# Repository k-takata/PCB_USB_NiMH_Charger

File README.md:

# USB NiMH ゆっくり充電器 (USB NiMH Slow Charger) rev. 3

## 概要

[秋月電子](https://akizukidenshi.com/)の[いたわりNiCd充電器 キット](https://akizukidenshi.com/img/contents/kairo/%E3%83%87%E3%83%BC%E3%82%BF/%E5%85%85%E9%9B%BB%E5%99%A8%E9%96%A2%E4%BF%82/H001%E3%81%84%E3%81%9F%E3%82%8F%E3%82%8ANiCd_.pdf)を元に、USBを電源とし、ニッケル水素電池を1本単位で単3、単4それぞれ2本（合計4本）まで充電できるようにした充電器です。

## 使用したソフトウェア

KiCad 7.0

## 回路図

## 基板パターン図

## 部品表

| Reference            |個数|値    | 説明 |
|----------------------|----|------|------|
|BT1, BT2              |   2|      |[単4電池ボックス](https://akizukidenshi.com/catalog/g/g102670/)|
|BT3, BT4              |   2|      |[単3電池ボックス](https://akizukidenshi.com/catalog/g/g100308/)|
|C1, C4, C5, C6, C7, C8|   6|0.1μF|積層セラミックコンデンサー|
|C2                    |   1|100μF|電解コンデンサー φ5[^1]|
|C3                    |   1| 10μF|[積層セラミックコンデンサー 10μF](https://akizukidenshi.com/catalog/g/g103095/)|
|D1                    |   1|[11EQS03L](https://akizukidenshi.com/catalog/g/g108997/)|ショットキーバリアダイオード|
|D2, D3, D4, D5        |   4|      |[低消費赤色LED](https://akizukidenshi.com/catalog/g/g116914/)。眩しい場合は[LED光拡散キャップ](https://akizukidenshi.com/catalog/g/g101120/)が使える。|
|F1                    |   1|  1.1A|[ポリヒューズ](https://akizukidenshi.com/catalog/g/g100507/)|
|J1                    |   1|UJC-HP-3-SMT-TR|[USB Type-C コネクター 電源供給用](https://akizukidenshi.com/catalog/g/g116438/)|
|J2                    |   1|      |ピンヘッダー 1x2、強制充電用|
|Q1                    |   1|2SA1015||
|Q2, Q3, Q4, Q5        |   4|[2SB834](https://akizukidenshi.com/catalog/g/g108747/)|裏面に取り付け。他の代替候補としては[2SA1441](https://akizukidenshi.com/catalog/g/g116790/)や[TTA008B](https://akizukidenshi.com/catalog/g/g109938/)、[2SB1185](https://akizukidenshi.com/catalog/g/g110994/) (h<sub>FE</sub> class E)などがある。（TTA008Bは2SB834などとはピン配置が異なるので裏返して取り付ける。）|
|R1, R2                |   2|5.1kΩ|緑茶赤金、小型|
|R3                    |   1| 10kΩ|茶黒橙金、半固定抵抗RV1と同じ値|
|R4, R5, R9, R13, R17  |   5| 10kΩ|茶黒橙金|
|R6, R10, R14, R18     |   4|  1MΩ|茶黒緑金|
|R7, R11               |   2|2.7kΩ|赤紫赤金、小型|
|R8, R12               |   2|  15Ω|茶緑黒金、1/2W 小型|
|R15, R19              |   2|1.6kΩ|茶青赤金、小型|
|R16, R20              |   2| 5.6Ω|緑青金金、1/2W 小型|
|RV1                   |   1| 10kΩ|抵抗R3と同じ値、[GF063P](https://akizukidenshi.com/catalog/g/g114905/)|
|U1                    |   1|[μPC339C](https://akizukidenshi.com/catalog/g/g112556/)|4回路入りコンパレーター、[LM339](https://akizukidenshi.com/catalog/g/g100436/)でも可|
|U2                    |   1|[S-812C33](https://akizukidenshi.com/catalog/g/g103289/)|低損失CMOS三端子レギュレーター 3.3V 50mA|

[^1]: このサイズならば、まっすぐ足が奥まで挿せる。

## いたわりNiCd充電器からの変更点

* 電源をACアダプターからUSB Type-Cに変更。
  - USB PD機器からも確実に電源を得られるようにするため、CC1, CC2には5.1kΩを接続。
  - 安全のため、ポリヒューズを使用。
* 充電を2本単位から1本単位に変更。
  - 基準電圧を5.0Vから3.3Vに変更。(U2をS-81350からS-812C33に変更。)
  - 温度補償用のダイオード1S2076A 2本をショットキーバリアダイオード1本に変更。  
    NiMH電池の充電終了時電圧には1本当たり約-3mV/Kの温度係数があります。PN接合には-2mV/Kの温度係数があることから、元の回路ではこれを3直列とし、2本分の-6mV/Kの補正を行っていました。ショットキーバリアダイオードの正確な温度係数は調べられませんでしたが、PN接合の温度係数より小さいよう(-1.0 ~ -1.5mV/K程度?)ですので、これをもって1本分の補正としています。
* 秋月電子の[B基板](https://akizukidenshi.com/catalog/r/rboard10)のサイズに実装できるよう、充電本数は単3、単4それぞれ2本に変更。
* 強制充電用にJ2を用意。
  - 通常充電モード: 通常、J2は接続して使います。充電終止電圧の監視が行われます。
  - 強制充電モード: J2を開放すると、Vrefは3.3Vに設定され、充電終止電圧の監視が行われません。  
    新品のNiMH電池の内部抵抗は0.1Ω程度のようですが、寿命が近づいてくると徐々に内部抵抗が大きくなります。例えば内部抵抗が10Ωにもなると、70mAの充電電流を流すと端子電圧が0.7Vも上昇するため、正常に充電電圧の監視を行うことはできません。こうなってしまうと通常の充電器では充電することができません。そのような場合でも強制充電モードを使えば充電が可能です。ただし、充電電圧の監視がなくなってしまいますので、10～15時間程度で電池を外すようにしてください。
* 充電電流(I<sub>Chg</sub>)は以下のように設定。
  - 単4: 約70mA (= 1.05V / 15Ω)
  - 単3: 約190mA (= 1.05V / 5.6Ω)
* LEDを低消費版に変更し、LM339で直接駆動するように変更。
  - 2SC1815を削除。
  - プルアップ抵抗を削除。
  - R7, R11を、680Ωから2.7kΩに変更し、R15, R19を、680Ωから1.6kΩに変更。  
    2SB834のh<sub>FE</sub>を150程度と想定し、LEDの電流(I<sub>LED</sub>)が0.8mA程度となるように設定しています。
    - 単4の場合:  
      I<sub>B</sub> = I<sub>Chg</sub> / h<sub>FE</sub> = 70 / 150 = 0.47mA  
      R7, R11に流れる電流は I<sub>B</sub> + I<sub>LED</sub> = 0.47 + 0.8 = 1.27mA  
      抵抗値は (5.0V - 1.7V) / 1.27mA = 2.60kΩ
    - 単3の場合:  
      I<sub>B</sub> = I<sub>Chg</sub> / h<sub>FE</sub> = 190 / 150 = 1.27mA  
      R15, R19に流れる電流は I<sub>B</sub> + I<sub>LED</sub> = 1.27 + 0.8 = 2.07mA  
      抵抗値は (5.0V - 1.7V) / 1.27mA = 1.59kΩ
* 2SB948が入手できなかったので、簡単に入手できた2SB834に変更。
* RV1の回転方向を逆にし、右に回すほどVrefが高くなるように変更。

## rev. 1 あるいは rev. 2 からの変更点

* 充電本数を単3 2本から、単3、単4それぞれ2本（合計4本）に変更。
  - これに伴い、J2, J3による単3/単4切り替えは廃止。
  - 充電本数を増やしたことによる部品の増加に対応するため、上述の通りLEDを低消費版に変更することで部品を削減。レイアウトを大幅変更。
* USB Type-Cコネクターを秋月電子のDIP化キットから、直付けに変更。
* その他、使用部品の見直し。

## 調整

J2を接続し、RV1を右に回しきって、700mAhの単4なら15時間程度、2000mAhの単3なら16時間程度充電します。その後電池を外して20分程度置いてから、再度電池を入れます。RV1を回して、LEDが点滅する位置に合わせて終了です。Vrefの電圧は1.40~1.45V程度になっているのが想定です。

## 完成品

## License

CC0

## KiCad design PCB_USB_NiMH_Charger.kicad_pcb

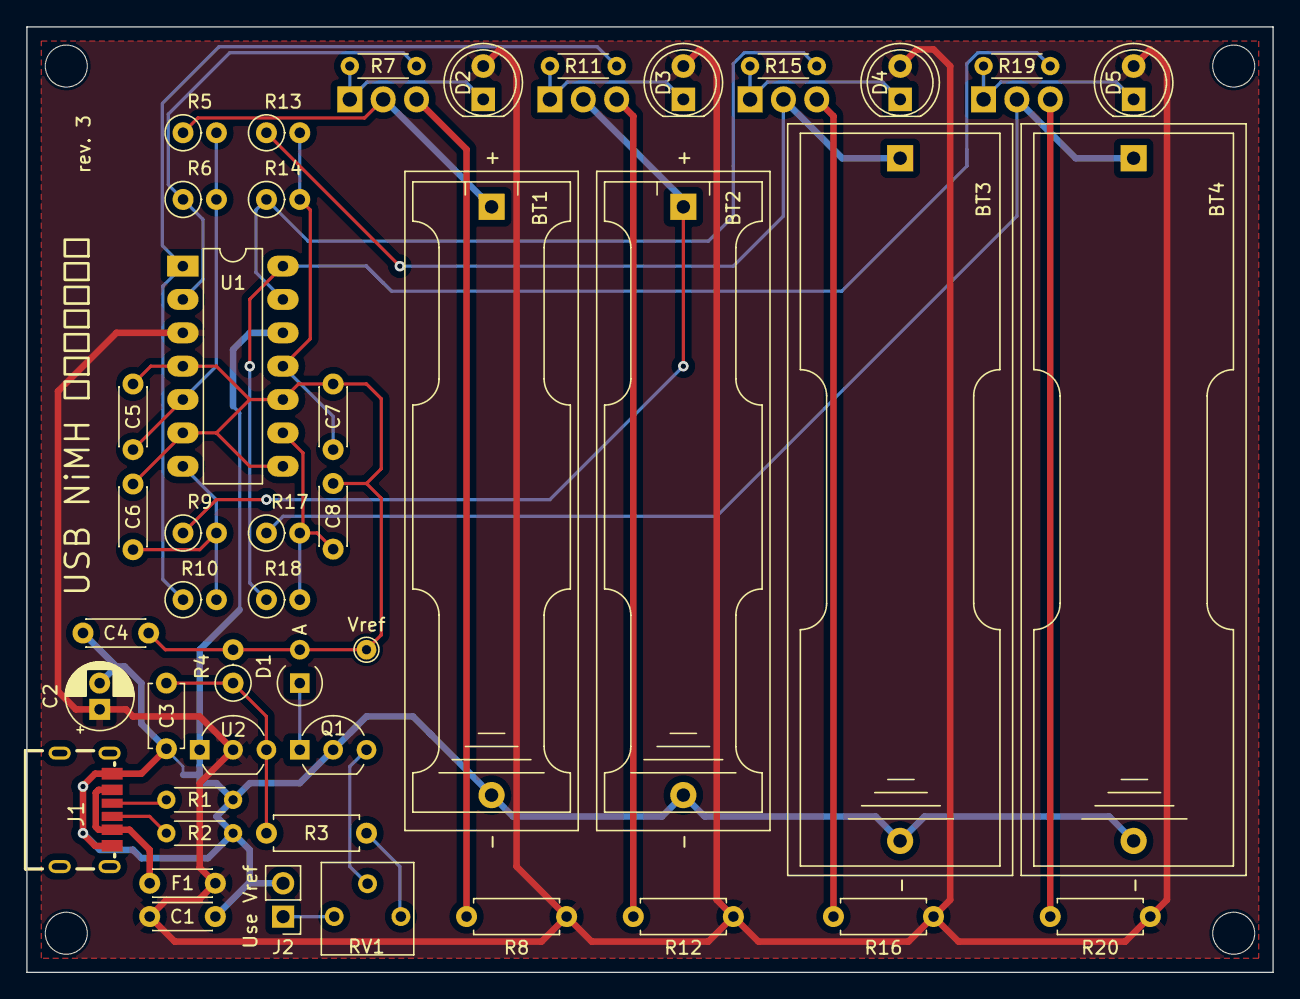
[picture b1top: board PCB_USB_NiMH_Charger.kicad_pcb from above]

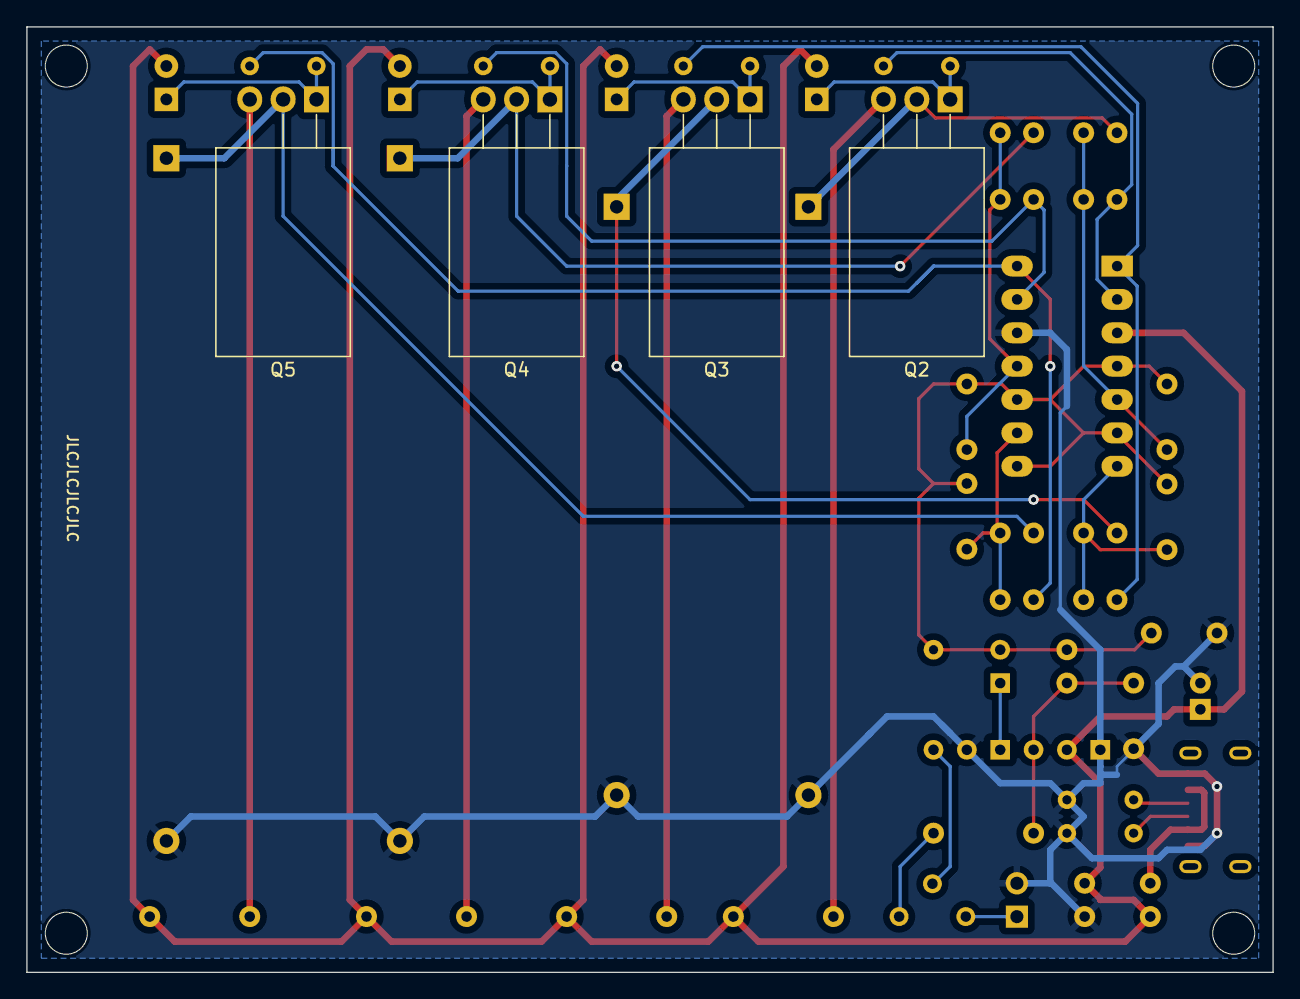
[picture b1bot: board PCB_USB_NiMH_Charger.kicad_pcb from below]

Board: 2 copper layers, 94.9 x 72.0 mm, 53 parts (4 on the bottom side), 31 nets.

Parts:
BT1, BT2: Battery_Cell (AAA); BatteryHolder_COMF_BH-411-4P24_1xAAA
BT3, BT4: Battery_Cell (AA); BatteryHolder_Keystone_2460_1xAA
C1, C4, C5, C6, C7, C8: 0.1u; C_Disc_D4.3mm_W1.9mm_P5.00mm
C2: 100u; CP_Radial_D5.0mm_P2.00mm
C3: 10u; C_Disc_D4.7mm_W2.5mm_P5.00mm
D1: 11EQS03L; D_DO-41_SOD81_P2.54mm_Vertical_AnodeUp
D2, D3, D4, D5: LED; LED_D5.0mm
F1: Polyfuse; C_Disc_D4.3mm_W1.9mm_P5.00mm
H1, H2, H3, H4: MountingHole; MountingHole_3.2mm_M3
J1: USB_C_Receptacle_Simple; USB_C_Receptacle_CUI_Devices_UJC-HP-3-SMT-TR
J2: Conn_02x01; PinHeader_1x02_P2.54mm_Vertical
Q1: 2SA1015; TO-92_Inline_Wide
Q2, Q3, Q4, Q5: 2SB834; TO-220-3_Horizontal_TabDown
R1, R2: 5.1k; R_Axial_DIN0204_L3.6mm_D1.6mm_P5.08mm_Horizontal
R3: 10k; R_Axial_DIN0207_L6.3mm_D2.5mm_P7.62mm_Horizontal
R4, R5, R9, R13, R17: 10k; R_Axial_DIN0207_L6.3mm_D2.5mm_P2.54mm_Vertical
R6, R10, R14, R18: 1M; R_Axial_DIN0207_L6.3mm_D2.5mm_P2.54mm_Vertical
R7, R11: 2.7k; R_Axial_DIN0204_L3.6mm_D1.6mm_P5.08mm_Horizontal
R8, R12: 15; R_Axial_DIN0207_L6.3mm_D2.5mm_P7.62mm_Horizontal
R15, R19: 1.6k; R_Axial_DIN0204_L3.6mm_D1.6mm_P5.08mm_Horizontal
R16, R20: 5.6; R_Axial_DIN0207_L6.3mm_D2.5mm_P7.62mm_Horizontal
RV1: 10k; Potentiometer_TOCOS_GF063P_Vertical
TP1: Vref; TestPoint_THTPad_D1.5mm_Drill0.7mm
U1: LM339; DIP-14_W7.62mm_LongPads
U2: S-812C33A_TO92; TO-92_Inline_Wide

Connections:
+5V: C1.1, C2.1, D2.2 (A), D3.2 (A), D4.2 (A), D5.2 (A), F1.2, R8.1, R12.1, R16.1, R20.1, U1.3 (V+), U2.2 (VI)
/+3.3V: C3.1, R3.2, R4.1, U2.3 (VO)
/VBUS: F1.1, J1.A9 (VBUS), J1.B9 (VBUS)
GND: BT1.2 (-), BT2.2 (-), BT3.2 (-), BT4.2 (-), C1.2, C2.2, C3.2, C4.2, J1.A12 (GND), J1.B12 (GND), J2.2, Q1.2 (C), R1.1, R2.1, U1.12 (V-), U2.1 (VSS)
unnamed: BT1.1 (+), Q2.2 (C), R5.1
unnamed: BT2.1 (+), Q3.2 (C), R9.1
unnamed: BT3.1 (+), Q4.2 (C), R13.1
unnamed: BT4.1 (+), Q5.2 (C), R17.1
unnamed: D1.1 (K), Q1.1 (E)
unnamed: D2.1 (K), Q2.1 (B), R7.1
unnamed: D3.1 (K), Q3.1 (B), R11.1
unnamed: D4.1 (K), Q4.1 (B), R15.1
unnamed: D5.1 (K), Q5.1 (B), R19.1
unnamed: J1.A5 (CC1), R1.2
unnamed: J1.B5 (CC2), R2.2
unnamed: J2.1, RV1.1
unnamed: Q1.3 (B), RV1.2
unnamed: Q2.3 (E), R8.2
unnamed: Q3.3 (E), R12.2
unnamed: Q4.3 (E), R16.2
unnamed: Q5.3 (E), R20.2
unnamed: R3.1, RV1.3
unnamed: R6.1, R7.2, U1.2
unnamed: R10.1, R11.2, U1.1
unnamed: R14.1, R15.2, U1.13
unnamed: R18.1, R19.2, U1.14
unnamed: C5.1, R5.2, R6.2, U1.5 (+)
unnamed: C6.1, R9.2, R10.2, U1.7 (+)
unnamed: C7.1, R13.2, R14.2, U1.11 (+)
unnamed: C8.1, R17.2, R18.2, U1.9 (+)
Vref: C4.1, C5.2, C6.2, C7.2, C8.2, D1.2 (A), R4.2, TP1.1, U1.4 (-), U1.6 (-), U1.8 (-), U1.10 (-)

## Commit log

2023-03-11 Initial commit
    Add `.gitignore`.
2023-03-11 Add schematics and pcb
2023-03-12 Add .gitignore
2023-03-12 Add README.md
2023-03-12 doc: Change image URL
2023-03-12 doc: Adjust parts list
2023-03-12 WIP: Change 2-battery circuit to 4-battery circuit
    Change LM393 to LM339.
2023-03-14 配線一旦削除
2023-03-15 Change BT1 and BT2 to AAA from AA
2023-03-17 doc: Update README
    Add some links.
2023-03-18 doc: 完成品の写真を追加
2023-03-18 doc: 抵抗のカラーコードを追加
2023-03-20 doc: C2のサイズを変更
2023-03-20 doc: Fix typo
2023-03-21 初版の知見を反映した細かい調整
    * VBUSをラベル付け。
    * USBコネクタのパッドの穴のサイズを0.9mmに縮小。
    * ネットクラスに "Power" を追加。
    * D1用にDO-41Sのフットプリントを追加。
    * R8, R9, R14, R15 の配置を調整。
    * 配線を調整。
2023-03-21 パッドとベタの接続形状を調整
2023-03-21 Add rev. 2 silk
    * rev. 2 のシルクを追加。
    * 配線の表裏を調整。
2023-03-22 Update title to rev. 2
2023-03-23 doc: Update README.md
    J3, J4の設定について少し追記。
2023-03-26 Update to rev. 3
    * LED を低消費電力版に変更し、LM339 で直接駆動するように変更。
    - 2SC1815 (2SC2458) を削除。
    - プルアップ抵抗を削除。
    - 680Ω を 2KΩ に変更。
    * 10μF 電解コンデンサーを積層セラミックコンデンサーに変更。
    * 2SB834 を裏面に配置。
2023-03-26 Import the latest README from the master branch
2023-03-26 doc: Update document and images
2023-03-26 配線を調整
2023-03-27 微調整
    * 配線を調整。
    * BT1, BT2のパッド位置を調整。(マイナス側を0.2mm外側へ移動。)
2023-03-27 doc: Update README
    4本充電バージョンのリンクを記載
2023-03-27 Update BT1, BT2
    BT1, BT2のフットプリントを秋月電子公開のデータシートに従って更新。
2023-03-27 C6, C7, C8の配置を修正
2023-03-27 小修正
    * Gerber job ファイルを出力しない。
    * フットプリントの不一致を無視。
    * 基板パターン図を更新。
2023-03-28 配線調整
2023-03-28 抵抗値を調整
    R7, R11, R15, R19を充電電流に合わせて調整。
2023-03-28 doc: Update README
    抵抗値の算出根拠を記載。
2023-03-28 doc: Update README
    調整方法を更新。
2023-03-28 抵抗値を変更
2023-03-28 半固定抵抗のフットプリントを修正
2023-03-29 Update doc
2023-03-29 Update PCB pattern
2023-03-29 Update revision
2023-03-29 Update title and revision
2023-03-29 Update README
    Add revision.
2023-03-30 Update README
    rev. 1 あるいは rev. 2 からの変更点を記載。
2023-03-30 基板外形を調整
2023-03-30 Update drill origin
2023-03-30 Adjust schema layout
2023-04-01 Update 3D models
2023-04-03 Update README.md
    LED光拡散キャップへのリンクを追加。
2023-04-11 完成品の写真を掲載
2023-04-17 Update README
    2SB834の代替として、2SA1441とTTA008Bを記載。
2023-04-18 Update schema
2023-04-19 Update thumbnail
2023-04-19 Update README
    Mention about 2SB1185.
2023-04-19 Update footprint of GF063P
2024-01-26 Update links
    秋月電子のサイトリニューアルに対応。
